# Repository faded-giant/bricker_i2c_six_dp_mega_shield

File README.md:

Usage:

example_bricker_i2c.vi contains an example on how to use bricker_arduino_i2c.vi in an existing LabVIEW project. It is important to use a "stop" button, initializaton and closure unit as demonstrated to maintain control of the device.

The arduino is set up to detect configuration changes (number of sensors present and what position they are installed in) automatically, as seen below. The VI outputs an array of 6 pressure strings and 6 temperature strings.

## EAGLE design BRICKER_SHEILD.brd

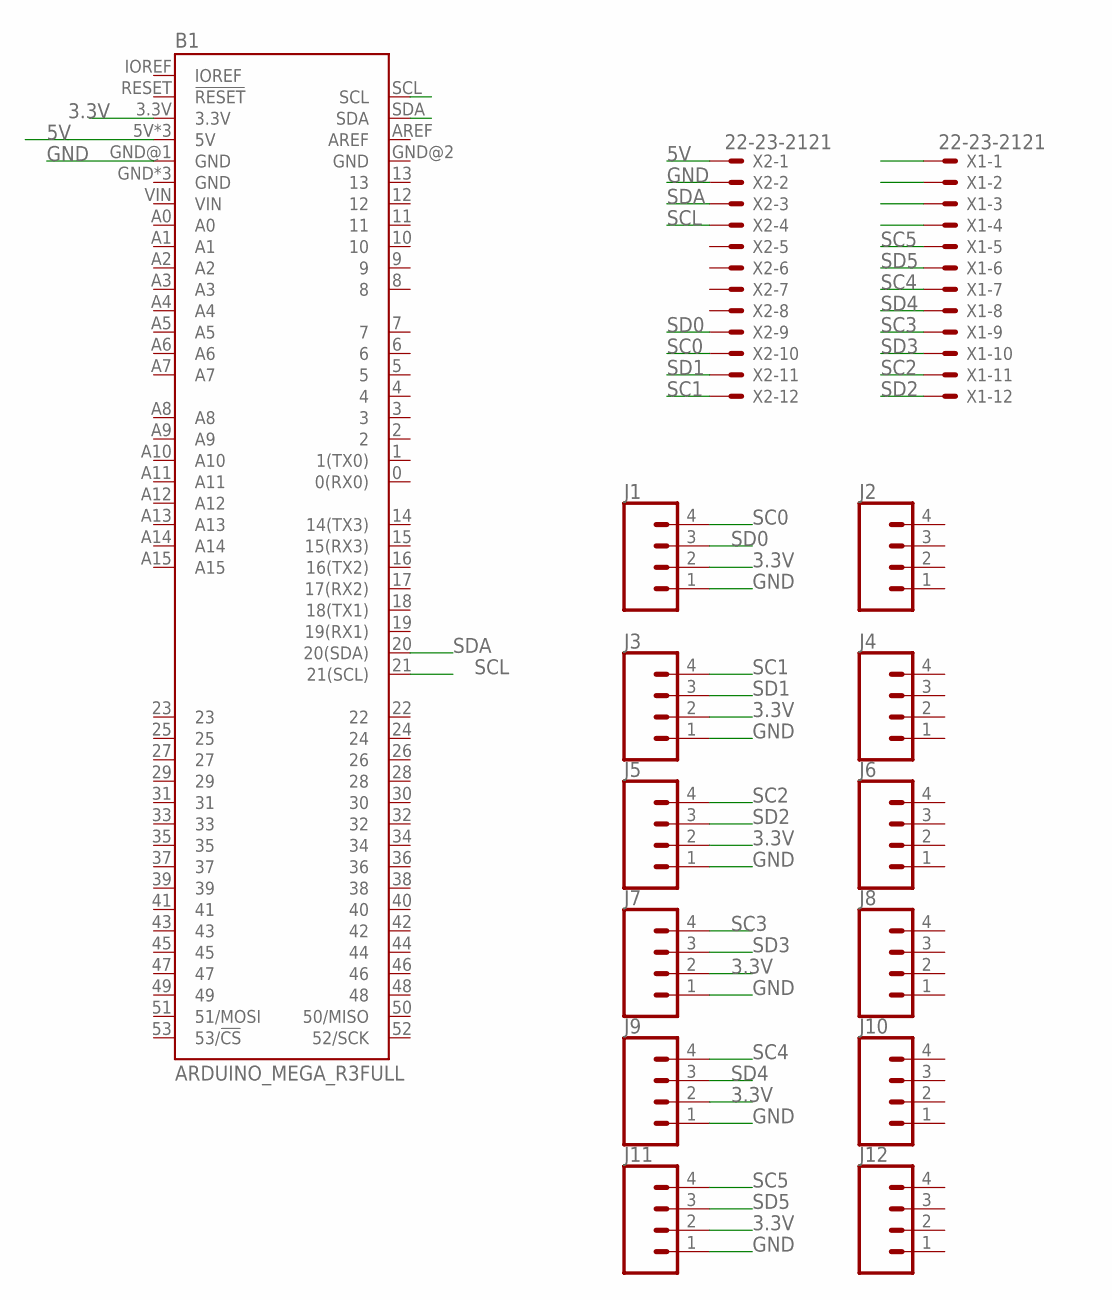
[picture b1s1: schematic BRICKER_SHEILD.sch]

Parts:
B1: ARDUINO_MEGA_R3FULL; ARDUINO_MEGA_NO_SILK
J1, J2, J3, J4, J5, J6, J7, J8, J9, J10, J11, J12: CONN_041X04_NO_SILK; 1X04_NO_SILK
X1, X2: 22-23-2121

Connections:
3.3V: B1.3.3V, J1.2, J3.2, J5.2, J7.2, J9.2, J11.2
5V: B1.5V, B1.5V@1 (5V), B1.5V@2 (5V), X2.1
GND: B1.GND@1 (GND), J1.1, J3.1, J5.1, J7.1, J9.1, J11.1, X2.2
SC0: J1.4, X2.10
SC1: J3.4, X2.12
SC2: J5.4, X1.11
SC3: J7.4, X1.9
SC4: J9.4, X1.7
SC5: J11.4, X1.5
SCL: B1.21 (21(SCL)), X2.4
SD0: J1.3, X2.9
SD1: J3.3, X2.11
SD2: J5.3, X1.12
SD3: J7.3, X1.10
SD4: J9.3, X1.8
SD5: J11.3, X1.6
SDA: B1.20 (20(SDA)), X2.3

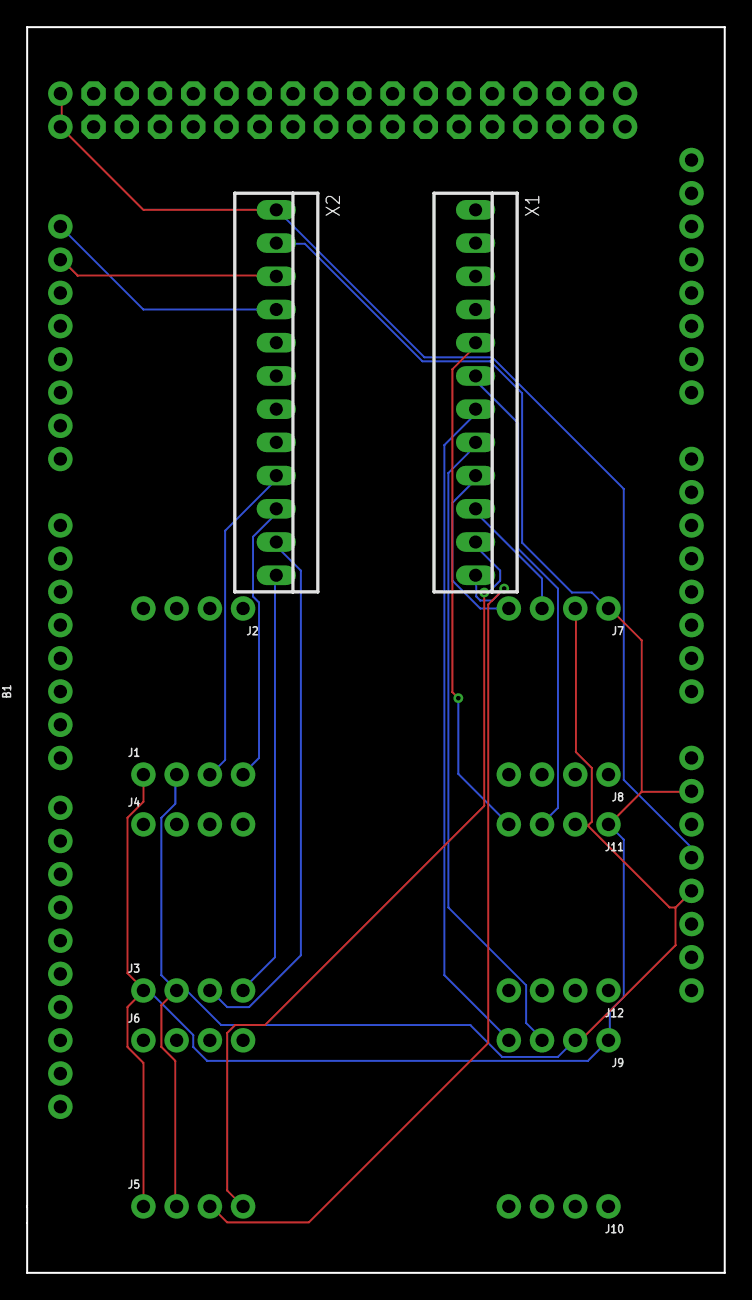
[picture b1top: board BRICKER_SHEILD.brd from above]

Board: 2 copper layers, 53.3 x 95.2 mm, 15 parts (0 on the bottom side), 17 nets.

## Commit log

2022-10-19 added source files

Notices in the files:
parts and their libraries:
SparkFun-Boards: Licensing: Creative Commons ShareAlike 4.0 International - https://creativecommons.org/licenses/by-sa/4.0
